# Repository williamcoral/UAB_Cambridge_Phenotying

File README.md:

# UAB_Cambridge_Phenotying
Weight Measuring Component
Hello Marius
This is the repository where you can find the requested circuit. Because some of the device features were not specified in your message, such as:
1. Sampling rate
2. Communication protocol for communication between sensors and microcontroller.
3. How to program the microcontroller and display the data.
4. Type of power supply to be used
5. Where the data will be displayed
6. Operating voltage
7. EMI-EMC

Thanks to this lack of information, I took certain liberties in the design of the circuit, such as:
1. Sampling rate will be 1k samples per second
2. The communication protocol will be I2C between the sensor and the microcontroller.
3. The microcontroller will be programmed through the usb port (micro USB connection). Data can be displayed using an OLED I2C panel or a computer, via the micro USB port.
4. This device will be able to work with at least two cell Lipo batteries (up to 3 cells 3S). as well as an external power supply or via a micro USB cable.
5. The data can be displayed using an OLED panel compatible with I2C communication or a computer through the USB port.
6. The input voltage range is from 4.5 to 21V.
7. mask on top and bottom layer.

I apologize in advance for taking so long to send the circuit, but from Thursday of last week to Tuesday of this week I was traveling. It was fun doing this circuit and I hope you like it.

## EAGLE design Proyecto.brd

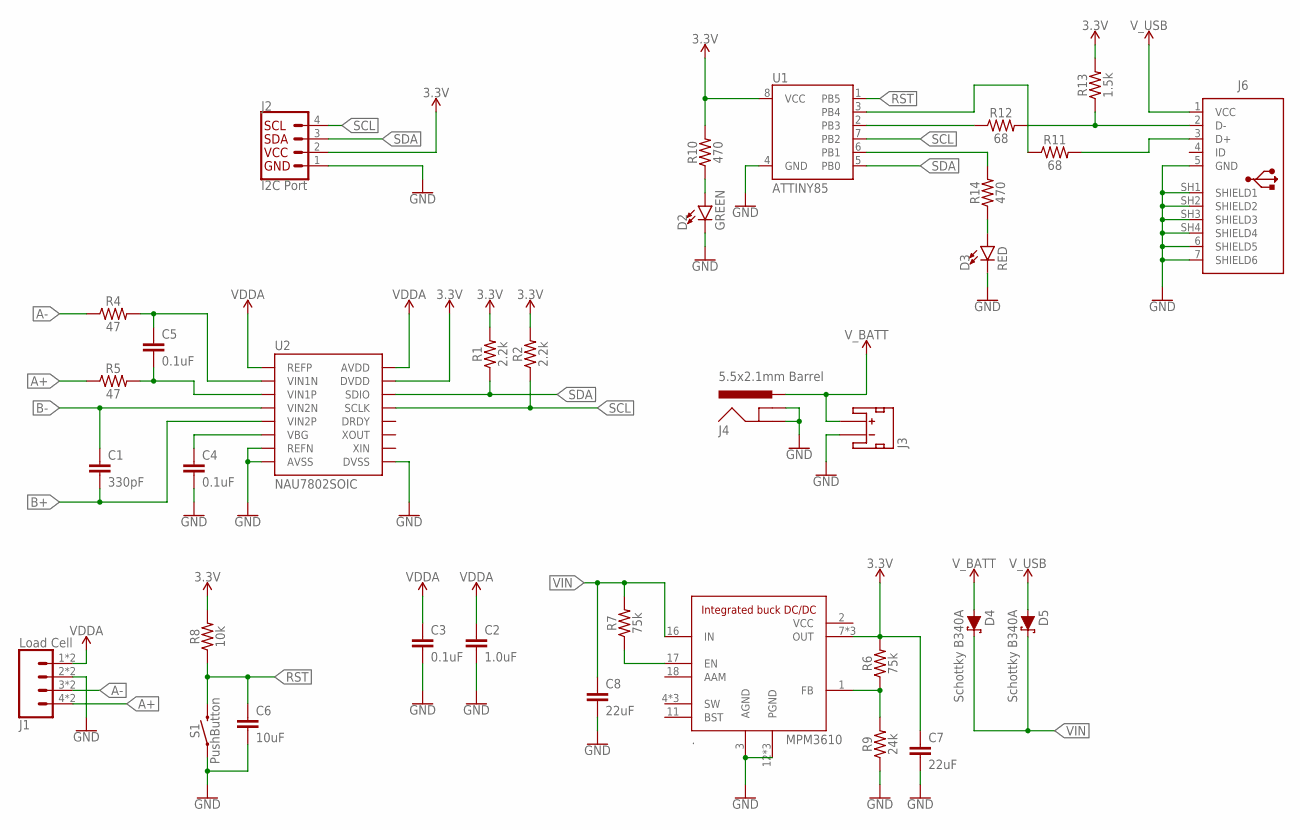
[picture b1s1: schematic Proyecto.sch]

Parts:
.: MPM3610; MICROBUILDER_MPM3610
C1: 330pF; 0603
C2: 1.0uF; 0603
C3, C4, C5: 0.1uF; 0603
C6: 10uF; 0603
C7, C8: 22uF; 1206
D2: GREEN; LED-0603
D3: RED; LED-0603
D4, D5: Schottky B340A; SMA-DIODE
J1: Load Cell; 1X04_SPRING_TERMINAL
J2: I2C Port; JST04_1MM_VERT
J3: JST_2MM_MALE; JST-2-SMD
J4: 5.5x2.1mm Barrel; POWER_JACK_SMD
J6: 10103594
R1, R2: 2.2k; 0603
R4, R5: 47; 0603
R6, R7: 75k; 0603
R8: 10k; 0603
R9: 24k; 0603
R10, R14: 470; 0603
R11, R12: 68; 0603
R13: 1.5k; 0603
S1: PushButton; TACTILE_SWITCH_SMD_5.2MM
U1: ATTINY85
U2: NAU7802SOIC; SO16

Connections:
3.3V: ..7 (OUT), ..8 (OUT), ..9 (OUT), C7.1, J2.2, R1.2, R2.2, R6.2, R8.2, R10.2, R13.2, U1.8 (VCC), U2.15 (DVDD)
A+: J1.4, J1.8 (4), R5.1
A-: J1.3, J1.7 (3), R4.1
B+: C1.2, U2.5 (VIN2P)
B-: C1.1, U2.4 (VIN2N)
GND: ..3 (AGND), ..12 (PGND), ..13 (PGND), ..14 (PGND), C2.2, C3.2, C4.2, C6.2, C7.2, C8.2, D2.C, D3.C, J1.2, J1.6 (2), J2.1, J3.1 (-), J4.GND (GNDBREAK), J4.P$4 (GND), R9.1, S1.1, S1.2 (1), U1.4 (GND), U2.7 (REFN), U2.8 (AVSS), U2.9 (DVSS)
unnamed: R11.1, U1.3 (PB4)
unnamed: C4.1, U2.6 (VBG)
unnamed: ..1 (FB), R6.1, R9.2
unnamed: D3.A, R14.1
unnamed: C5.1, R4.2, U2.2 (VIN1N)
unnamed: C5.2, R5.2, U2.3 (VIN1P)
unnamed: ..17 (EN), R7.1
unnamed: R14.2, U1.6 (PB1)
unnamed: J6.3 (D+), R11.2
unnamed: R12.1, U1.2 (PB3)
unnamed: J6.2 (D-), R12.2, R13.1
unnamed: D2.A, R10.1
RST: C6.1, R8.1, S1.3 (2), S1.4 (2), U1.1 (PB5)
SCL: J2.4, R2.1, U1.7 (PB2), U2.13 (SCLK)
SDA: J2.3, R1.1, U1.5 (PB0), U2.14 (SDIO)
SHIELD5: J6.5 (GND), J6.6 (SHIELD5), J6.7 (SHIELD6), J6.SH1 (SHIELD1), J6.SH2 (SHIELD2), J6.SH3 (SHIELD3), J6.SH4 (SHIELD4)
VCC: ..2 (VCC)
VDDA: C2.1, C3.1, J1.1, J1.5 (1), U2.1 (REFP), U2.16 (AVDD)
VIN: ..16 (IN), C8.1, D4.C, D5.C, R7.2
V_BATT: D4.A, J3.2 (+), J4.VIN0 (PWR)
V_USB: D5.A, J6.1 (VCC)

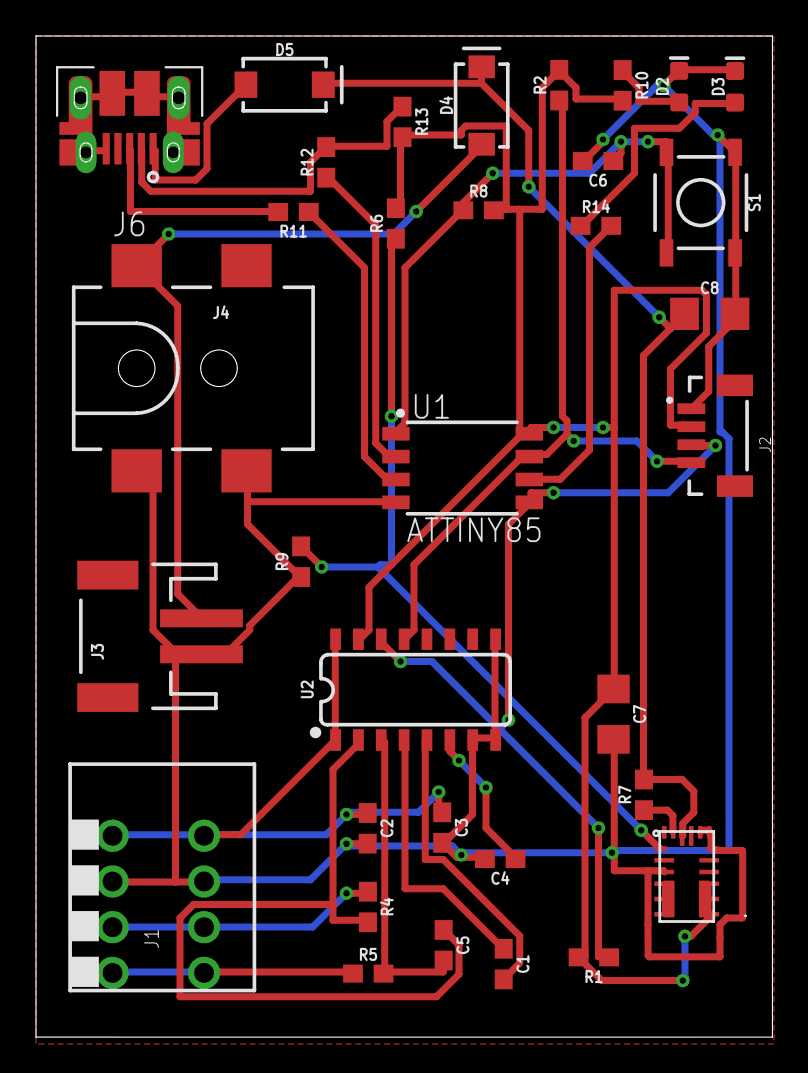
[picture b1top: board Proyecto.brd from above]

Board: 2 copper layers, 40.9 x 55.6 mm, 34 parts (0 on the bottom side), 26 nets.

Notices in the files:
parts and their libraries:
SparkFun-Capacitors: Licensing: Creative Commons ShareAlike 4.0 International - https://creativecommons.org/licenses/by-sa/4.0
